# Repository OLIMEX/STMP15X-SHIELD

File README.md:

# STMP15X-SHIELD
Shield for Industrial grade Linux Computer STMP157-OLinuXino which adds two UEXT, 40 GPIO, micro SD card

Product page: https://www.olimex.com/Products/OLinuXino/STMP1/STMP15X-SHIELD/open-source-hardware

## License
* Hardware is released under CERN Open Hardware Licence Version 2 - Strongly Reciprocal https://spdx.org/licenses/CERN-OHL-S-2.0.html
* Software is released under GPL3 License
* Documentation is released under CC BY-SA 3.0 https://creativecommons.org/licenses/by-sa/3.0/

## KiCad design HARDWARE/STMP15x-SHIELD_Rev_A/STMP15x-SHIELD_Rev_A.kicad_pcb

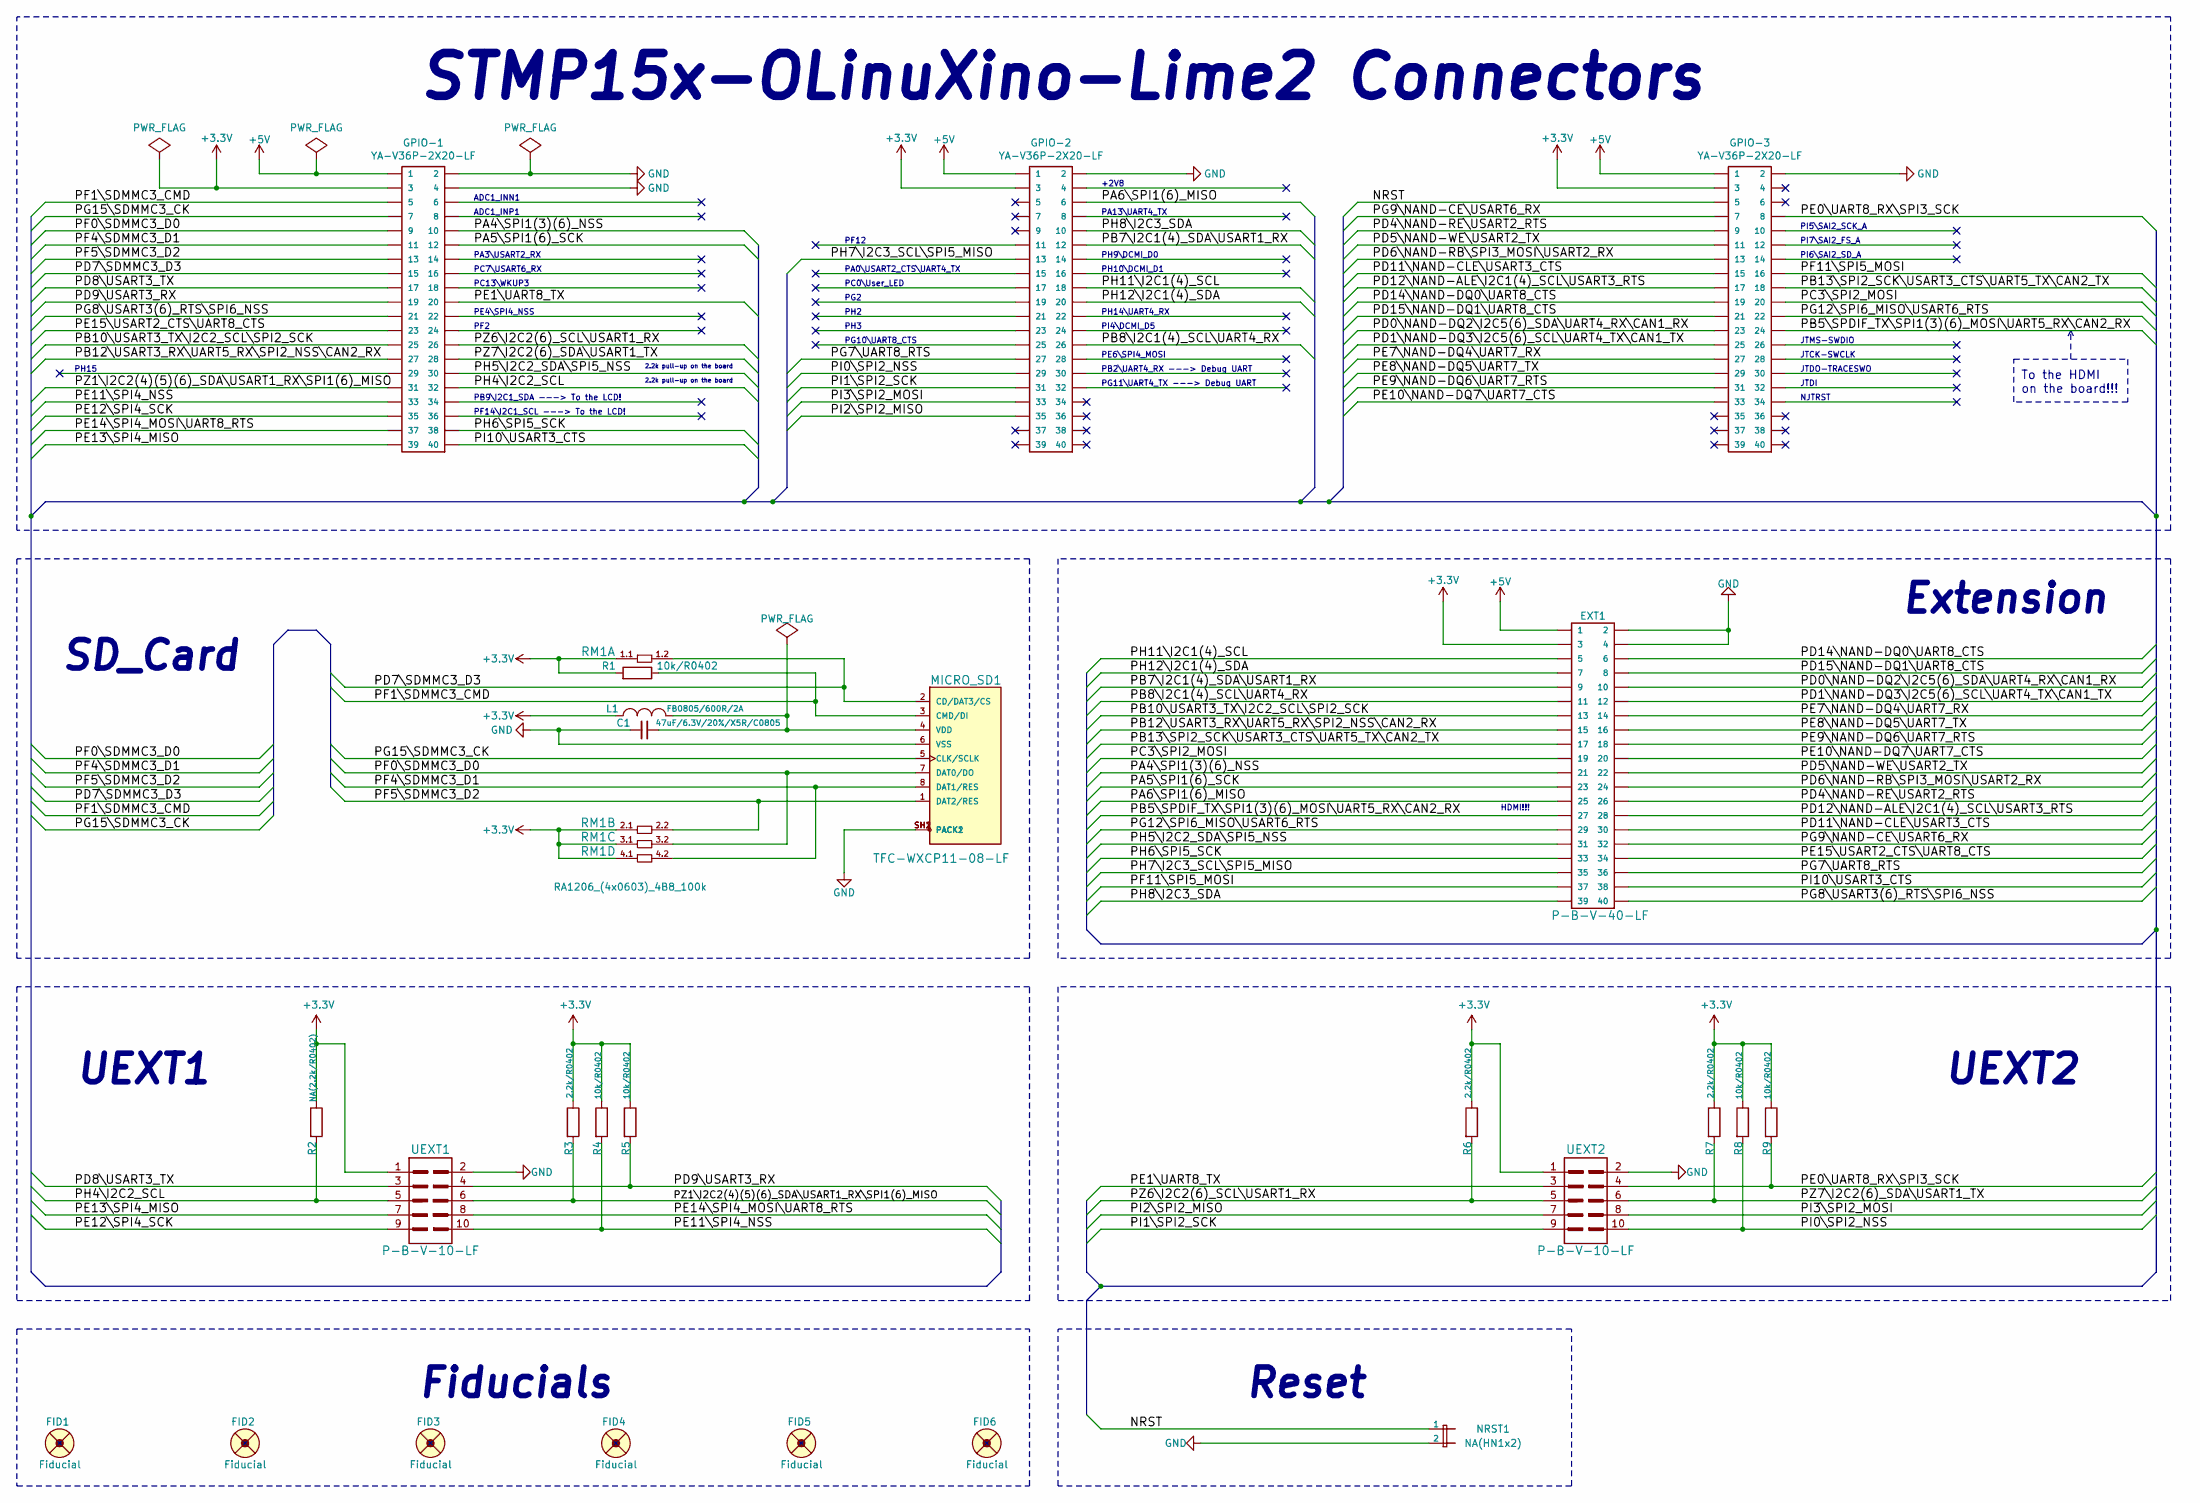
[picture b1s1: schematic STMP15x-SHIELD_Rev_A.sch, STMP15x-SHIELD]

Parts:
C1: 47uF/6.3V/20%/X5R/C0805; C_0805_5MIL_DWS
EXT1: P-B-V-40-LF; GBH-254-SMT-40
FID1, FID2, FID3, FID4, FID5, FID6: Fiducial; Fiducial1x3
GPIO-1, GPIO-2, GPIO-3: YA-V36P-2X20-LF; GPCB127SMT-02X20(YA-V36P-2X20-LF)
L1: FB0805/600R/2A; L_0805_5MIL_DWS
MICRO_SD1: TFC-WXCP11-08-LF
NRST1: NA(HN1x2); HN1x2_Jumper
R1, R4, R5, R8, R9: 10k/R0402; R_0402_5MIL_DWS
R2: NA(2.2k/R0402); R_0402_5MIL_DWS
R3, R6, R7: 2.2k/R0402; R_0402_5MIL_DWS
RM1: RA1206_(4x0603)_4B8_100k; RA1206_(4X0603)_4B8_xx
UEXT1, UEXT2: P-B-V-10-LF; GBH-254-SMT-10

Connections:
+3V3: EXT1.3, GPIO-1.3, GPIO-2.3, GPIO-3.3, L1.1, R1.2, R2.1, R3.1, R4.1, R5.1, R6.1, R7.1, R8.1, R9.1, RM1.1.1, RM1.2.1, RM1.3.1, RM1.4.1, UEXT1.1, UEXT2.1
+5V: EXT1.1, GPIO-1.1, GPIO-2.1, GPIO-3.1
/NRST: GPIO-3.5, NRST1.1
/PA4\SPI1(3)(6)_NSS: EXT1.21, GPIO-1.10
/PA5\SPI1(6)_SCK: EXT1.23, GPIO-1.12
/PA6\SPI1(6)_MISO: EXT1.25, GPIO-2.6
/PB5\SPDIF_TX\SPI1(3)(6)_MOSI\UART5_RX\CAN2_RX: EXT1.27, GPIO-3.24
/PB7\I2C1(4)_SDA\USART1_RX: EXT1.9, GPIO-2.12
/PB8\I2C1(4)_SCL\UART4_RX: EXT1.11, GPIO-2.26
/PB10\USART3_TX\I2C2_SCL\SPI2_SCK: EXT1.13, GPIO-1.25
/PB12\USART3_RX\UART5_RX\SPI2_NSS\CAN2_RX: EXT1.15, GPIO-1.27
/PB13\SPI2_SCK\USART3_CTS\UART5_TX\CAN2_TX: EXT1.17, GPIO-3.18
/PC3\SPI2_MOSI: EXT1.19, GPIO-3.20
/PD0\NAND-DQ2\I2C5(6)_SDA\UART4_RX\CAN1_RX: EXT1.10, GPIO-3.23
/PD1\NAND-DQ3\I2C5(6)_SCL\UART4_TX\CAN1_TX: EXT1.12, GPIO-3.25
/PD4\NAND-RE\USART2_RTS: EXT1.26, GPIO-3.9
/PD5\NAND-WE\USART2_TX: EXT1.22, GPIO-3.11
/PD6\NAND-RB\SPI3_MOSI\USART2_RX: EXT1.24, GPIO-3.13
/PD7\SDMMC3_D3: GPIO-1.15, MICRO_SD1.2 (CD/DAT3/CS), RM1.1.2
/PD8\USART3_TX: GPIO-1.17, UEXT1.3
/PD9\USART3_RX: GPIO-1.19, R5.2, UEXT1.4
/PD11\NAND-CLE\USART3_CTS: EXT1.30, GPIO-3.15
/PD12\NAND-ALE\I2C1(4)_SCL\USART3_RTS: EXT1.28, GPIO-3.17
/PD14\NAND-DQ0\UART8_CTS: EXT1.6, GPIO-3.19
/PD15\NAND-DQ1\UART8_CTS: EXT1.8, GPIO-3.21
/PE0\UART8_RX\SPI3_SCK: GPIO-3.8, R9.2, UEXT2.4
/PE1\UART8_TX: GPIO-1.20, UEXT2.3
/PE7\NAND-DQ4\UART7_RX: EXT1.14, GPIO-3.27
/PE8\NAND-DQ5\UART7_TX: EXT1.16, GPIO-3.29
/PE9\NAND-DQ6\UART7_RTS: EXT1.18, GPIO-3.31
/PE10\NAND-DQ7\UART7_CTS: EXT1.20, GPIO-3.33
/PE11\SPI4_NSS: GPIO-1.33, R4.2, UEXT1.10
/PE12\SPI4_SCK: GPIO-1.35, UEXT1.9
/PE13\SPI4_MISO: GPIO-1.39, UEXT1.7
/PE14\SPI4_MOSI\UART8_RTS: GPIO-1.37, UEXT1.8
/PE15\USART2_CTS\UART8_CTS: EXT1.34, GPIO-1.23
/PF0\SDMMC3_D0: GPIO-1.9, MICRO_SD1.7 (DAT0/DO), RM1.3.2
/PF1\SDMMC3_CMD: GPIO-1.5, MICRO_SD1.3 (CMD/DI), R1.1
/PF4\SDMMC3_D1: GPIO-1.11, MICRO_SD1.8 (DAT1/RES), RM1.4.2
/PF5\SDMMC3_D2: GPIO-1.13, MICRO_SD1.1 (DAT2/RES), RM1.2.2
/PF11\SPI5_MOSI: EXT1.37, GPIO-3.16
/PG7\UART8_RTS: EXT1.36, GPIO-2.27
/PG8\USART3(6)_RTS\SPI6_NSS: EXT1.40, GPIO-1.21
/PG9\NAND-CE\USART6_RX: EXT1.32, GPIO-3.7
/PG12\SPI6_MISO\USART6_RTS: EXT1.29, GPIO-3.22
/PG15\SDMMC3_CK: GPIO-1.7, MICRO_SD1.5 (CLK/SCLK)
/PH4\I2C2_SCL: GPIO-1.32, R2.2, UEXT1.5
/PH5\I2C2_SDA\SPI5_NSS: EXT1.31, GPIO-1.30
/PH6\SPI5_SCK: EXT1.33, GPIO-1.38
/PH7\I2C3_SCL\SPI5_MISO: EXT1.35, GPIO-2.13
/PH8\I2C3_SDA: EXT1.39, GPIO-2.10
/PH11\I2C1(4)_SCL: EXT1.5, GPIO-2.18
/PH12\I2C1(4)_SDA: EXT1.7, GPIO-2.20
/PI0\SPI2_NSS: GPIO-2.29, R8.2, UEXT2.10
/PI1\SPI2_SCK: GPIO-2.31, UEXT2.9
/PI2\SPI2_MISO: GPIO-2.35, UEXT2.7
/PI3\SPI2_MOSI: GPIO-2.33, UEXT2.8
/PI10\USART3_CTS: EXT1.38, GPIO-1.40
/PZ1\I2C2(4)(5)(6)_SDA\USART1_RX\SPI1(6)_MISO: GPIO-1.31, R3.2, UEXT1.6
/PZ6\I2C2(6)_SCL\USART1_RX: GPIO-1.26, R6.2, UEXT2.5
/PZ7\I2C2(6)_SDA\USART1_TX: GPIO-1.28, R7.2, UEXT2.6
GND: C1.2, EXT1.2, EXT1.4, GPIO-1.2, GPIO-1.4, GPIO-2.2, GPIO-3.2, MICRO_SD1.6 (VSS), MICRO_SD1.SH1 (PACK1), MICRO_SD1.SH2 (PACK2), NRST1.2, UEXT1.2, UEXT2.2
unnamed: C1.1, L1.2, MICRO_SD1.4 (VDD)

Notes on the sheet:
PB9\I2C1_SDA ---> To the LCD!
PF14\I2C1_SCL ---> To the LCD!
UEXT1
UEXT2
PB2\UART4_RX ---> Debug UART
PG11\UART4_TX ---> Debug UART
ADC1_INN1
ADC1_INP1
PF2
PH15
2.2k pull-up on the board
PC0\User_LED
PG2
PH2
PH3
PI4\DCMI_D5
PH10\DCMI_D1
PH9\DCMI_D0
PI5\SAI2_SCK_A
PI7\SAI2_FS_A
PI6\SAI2_SD_A
JTMS-SWDIO
JTCK-SWCLK
JTDO-TRACESWO
JTDI
NJTRST
To the HDMI on the board!!!
PC7\USART6_RX
PA13\UART4_TX
PH14\UART4_RX
PA3\USART2_RX
PG10\UART8_CTS
PA0\USART2_CTS\UART4_TX
PF12
PE6\SPI4_MOSI
PE4\SPI4_NSS
Extension
Fiducials
+2V8
PC13\WKUP3

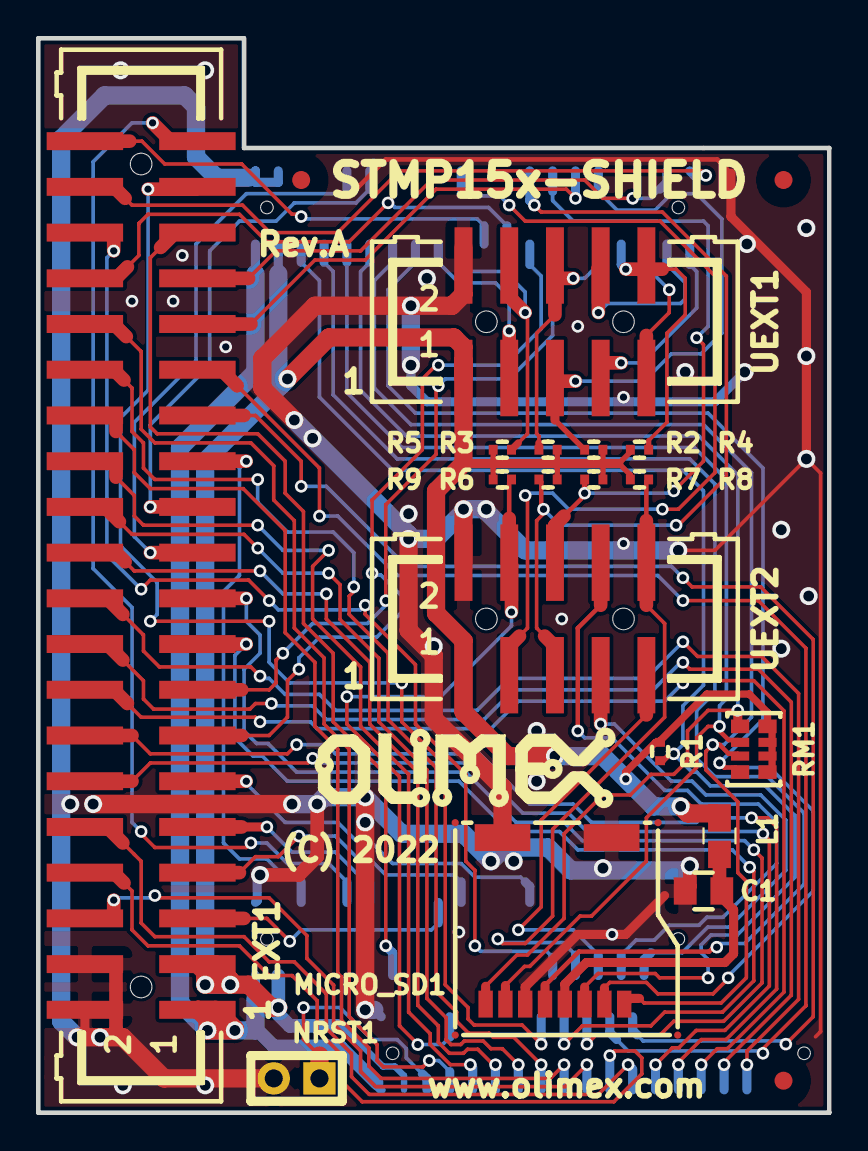
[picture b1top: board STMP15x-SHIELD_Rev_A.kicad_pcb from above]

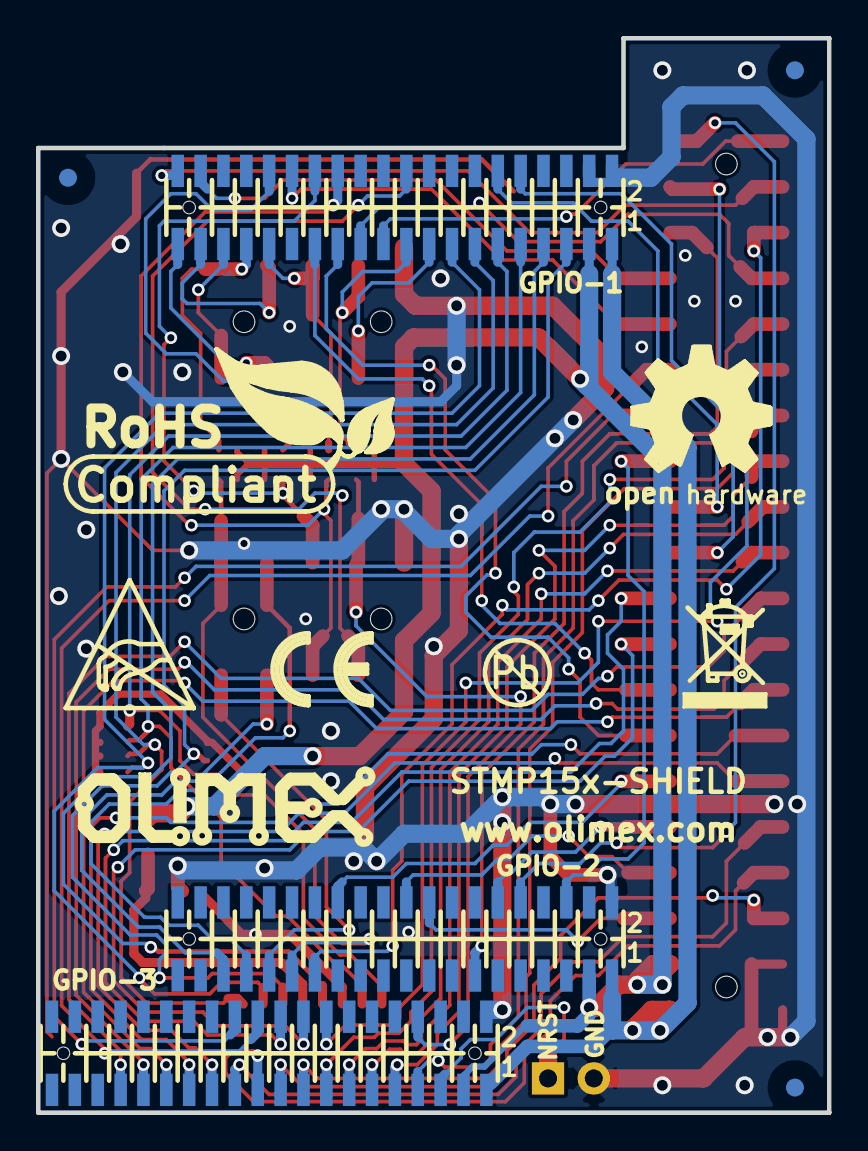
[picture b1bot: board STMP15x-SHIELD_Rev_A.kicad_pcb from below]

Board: 2 copper layers, 43.9 x 59.7 mm, 34 parts (13 on the bottom side), 63 nets.

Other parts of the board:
Logo_OSHW: LOGO_OPENHARDWARE_8x8
Logo_Olimex_1, Logo_Olimex_2: OLIMEX_LOGO_TB
Sign_Antistatic: LOGO_ANTISTATIC_1
Sign_CE: CE_Sign
Sign_PB-Free: LOGO_PBFREE
Sign_RecycleBin: LOGO_RECYCLEBIN_1
Sign_RoHS: LOGO_ROHS_1

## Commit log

2022-10-10 initial upload

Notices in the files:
HARDWARE/STMP15x-SHIELD_Rev_A/STMP15x-SHIELD_Rev_A.kicad_pcb:
(C) 2022
